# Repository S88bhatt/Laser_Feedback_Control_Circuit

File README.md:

# Laser Feedback Control Circuit
Contains all files in separate folders for the laser feedback control circuit.

## KiCAD
KiCAD Files that are up to date with the most recent and correct version of the circuit, including the PCB layout, schematic, and libraries for footprints and schematic components.

## Gimp
GIMP files which are used for laser cutting the box plating, allowing for a cleaner finish on the final product.

## FreeCAD
FreeCAD files are currently used to cut the box plating into the correct shape.

## Images
Images that show what the physical board looks like once complete.

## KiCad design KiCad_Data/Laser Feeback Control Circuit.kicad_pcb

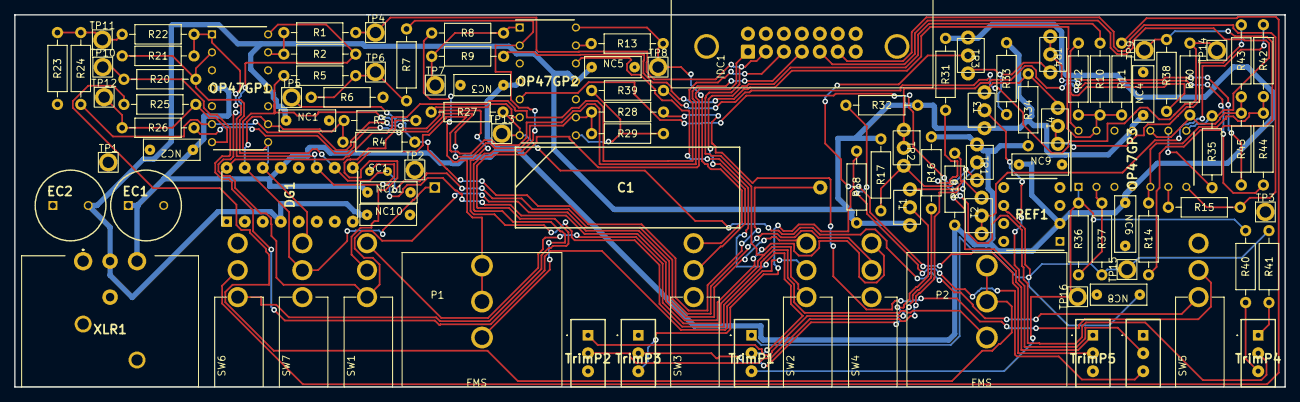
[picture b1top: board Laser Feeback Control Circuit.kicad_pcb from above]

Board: 2 copper layers, 179.6 x 52.6 mm, 105 parts (1 on the bottom side), 65 nets.

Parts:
C1: 1uF; Polypropylene Capacitor
DG1: P/N: ADG201AKNZ; ADG201AKNZ
EC1, EC2: 1000uF; ELECTROLYTIC CAPACITOR - EEU-EB1C102
IDC1: Male 14 Position IDC Connector, Digikey P/N: 609-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; Male IDC Connector
NC1, NC2, NC3, NC4, NC5, NC6, NC8, NC9, NC10, NC11: 0.1uF; CAPACITOR - 399-4209-ND
OP47GP1, OP47GP2, OP47GP3: OP470GPZ
P1, P2: 50k; Potentiometer
R1, R2, R3, R4, R8, R9, R10, R11, R12, R14, R17, R19, R20, R21, R26, R28, R29, R33, R34, R36, R37: 10k; R_Axial_DIN0207_L6.3mm_D2.5mm_P10.16mm_Horizontal
R5, R22, R38, R39, R42, R43, R44, R45: 0k; R_Axial_DIN0207_L6.3mm_D2.5mm_P10.16mm_Horizontal
R6, R23: Open; R_Axial_DIN0207_L6.3mm_D2.5mm_P10.16mm_Horizontal
R7, R13, R15, R24, R25, R27, R35: 1k; R_Axial_DIN0207_L6.3mm_D2.5mm_P10.16mm_Horizontal
R16, R18: 5k; R_Axial_DIN0207_L6.3mm_D2.5mm_P10.16mm_Horizontal
R30, R31, R32, R40, R41: 20k; R_Axial_DIN0207_L6.3mm_D2.5mm_P10.16mm_Horizontal
REF1: REF02 P/N: REF02CPZ; REF02CPZ
SC1: 1nF; Small Capacitor
SW1, SW2, SW3, SW4, SW5, SW6, SW7: SPDT Switch, P/N: 7101SD9AV2BE; AV2_Switch
T1, T2, T3, T4: Transistor P/N: 2N3906; Both_Transisitor
TP1, TP2, TP3, TP4, TP5, TP6, TP7, TP8, TP9, TP10, TP11, TP12, TP13, TP14, TP15, TP16: TestPoint
TR1, TR2, TR3, TR4: Transistor P/N: 2N3904; Both_Transisitor
TrimP1: 20k; 3296X1104LF -TrimPot
TrimP2, TrimP3, TrimP4: 10k; 3296X1104LF -TrimPot
TrimP5, TrimP6: 5k; 3296X1104LF -TrimPot
XLR1: XLR P/N: NC3MBH; NC3MBH_XLR

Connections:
+5V: NC8.1 (2), R37.1, R41.2, REF1.6 (VOUT), TP15.1, TrimP1.1
+15V: DG1.13 (V+), EC1.1, NC2.1 (2), NC3.1 (2), NC6.1 (2), NC9.1 (2), NC11.1 (2), OP47GP1.4 (+V), OP47GP2.4 (+V), OP47GP3.4 (+V), R16.1, R19.1, R31.1, R34.1, REF1.2 (VIN), TR1.1 (C), TR3.1 (C), XLR1.2 (+15V)
-5V: OP47GP3.1, R36.2, R40.1, TP16.1, TrimP1.3
-15V: DG1.4 (V-), EC2.2, NC1.1 (2), NC4.1 (2), NC5.1 (2), NC10.1 (2), OP47GP1.11 (V-), OP47GP2.11 (V-), OP47GP3.11 (V-), R17.1, R18.2, R32.2, R33.1, T1.1 (C), T3.1 (C), XLR1.3 (-15V)
GND: DG1.5 (GND), EC1.2, EC2.1, IDC1.7 (C), IDC1.8 (G), IDC1.9 (G), IDC1.10 (G), IDC1.11 (G), IDC1.12 (G), IDC1.13 (G), IDC1.14 (G), NC1.2 (1), NC2.2 (1), NC3.2 (1), NC4.2 (1), NC5.2 (1), NC6.2 (1), NC8.2 (1), NC9.2 (1), NC10.2 (1), NC11.2 (1), OP47GP1.3 (+), OP47GP1.5 (+), OP47GP1.10 (+), OP47GP1.12 (+), OP47GP2.3 (+), OP47GP2.10 (+), OP47GP3.3 (+), OP47GP3.12 (+), R6.1, R23.2, REF1.4 (GND), SW3.1 (A), SW5.3 (C), SW6.3 (C), TP1.1, TP2.1, TP3.1, TrimP2.3, TrimP3.1, TrimP5.3, TrimP6.1, XLR1.1 (GNDC), XLR1.G1
unnamed: C1.1, DG1.15 (D2), OP47GP1.9 (-), R3.2, R4.1, SW7.2 (B)
unnamed: DG1.16 (IN2), IDC1.3 (C)
unnamed: C1.2, DG1.14 (S2), OP47GP1.8, R4.2, R5.1, SW7.3 (C)
unnamed: DG1.10 (D3), OP47GP1.2 (-), R20.2, R21.1, SC1.1, SW4.2 (B)
unnamed: DG1.9 (IN3), IDC1.4 (C)
unnamed: DG1.11 (S3), OP47GP1.1, R21.2, R22.1, SC1.2, SW4.3 (C)
unnamed: IDC1.5 (C), OP47GP3.8, R35.2
unnamed: IDC1.6 (C), OP47GP3.7, R15.2
unnamed: OP47GP1.7, R25.2, R26.1, TP12.1
unnamed: OP47GP1.6 (-), P2.1, R24.2
unnamed: OP47GP1.13 (-), R1.2, R2.1
unnamed: OP47GP2.1, R8.2, R9.1, TP7.1
unnamed: OP47GP2.8, R29.2, R39.1
unnamed: OP47GP2.2 (-), P1.1, R7.2
unnamed: OP47GP2.5 (+), TrimP4.2
unnamed: OP47GP2.6 (-), R27.1
unnamed: OP47GP2.9 (-), R26.2, R28.1, R29.1
unnamed: OP47GP2.12 (+), TrimP1.2
unnamed: OP47GP2.13 (-), R13.1
unnamed: OP47GP3.14, R12.2, R38.1
unnamed: OP47GP3.2 (-), R36.1, R37.2
unnamed: OP47GP3.5 (+), R14.2, R42.2, R44.2
unnamed: OP47GP3.6 (-), R15.1
unnamed: OP47GP3.10 (+), R30.2, R43.2, R45.2
unnamed: OP47GP3.9 (-), R35.1
unnamed: OP47GP3.13 (-), R9.2, R10.1, R11.2, R12.1
unnamed: P1.2, P1.3, R8.1
unnamed: P2.2, P2.3, R25.1
unnamed: R5.2, R6.2, R7.1, TP6.1
unnamed: R14.1, R38.2, TP9.1
unnamed: R16.2, TrimP2.1
unnamed: R18.1, TrimP3.3
unnamed: R22.2, R23.1, R24.1, TP11.1
unnamed: R30.1, R39.2, TP14.1
unnamed: R31.2, TrimP5.1
unnamed: R32.1, TrimP6.3
unnamed: R40.2, TrimP4.3
unnamed: R41.1, TrimP4.1
unnamed: OP47GP1.14, R2.2, SW1.1 (A), SW2.3 (C)
unnamed: R3.1, SW1.2 (B), TP5.1
unnamed: IDC1.2 (C), R1.1, SW1.3 (C), SW2.1 (A), TP4.1
unnamed: R20.1, SW2.2 (B), TP10.1
unnamed: R10.2, SW3.2 (B)
unnamed: OP47GP2.14, R13.2, SW3.3 (C), TP8.1
unnamed: OP47GP2.7, R27.2, SW5.1 (A), TP13.1
unnamed: R28.2, SW5.2 (B)
unnamed: IDC1.1 (C), SW6.1 (A)
unnamed: R11.1, SW6.2 (B)
unnamed: T1.2 (B), TrimP3.2
unnamed: R19.2, T1.3 (E), T2.3 (E)
unnamed: R42.1, T2.1 (C), T2.2 (B)
unnamed: T3.2 (B), TrimP6.2
unnamed: R34.2, T3.3 (E), T4.3 (E)
unnamed: R43.1, T4.1 (C), T4.2 (B)
unnamed: TR1.2 (B), TrimP2.2
unnamed: R17.2, TR1.3 (E), TR2.3 (E)
unnamed: R44.1, TR2.1 (C), TR2.2 (B)
unnamed: TR3.2 (B), TrimP5.2
unnamed: R33.2, TR3.3 (E), TR4.3 (E)
unnamed: R45.1, TR4.1 (C), TR4.2 (B)

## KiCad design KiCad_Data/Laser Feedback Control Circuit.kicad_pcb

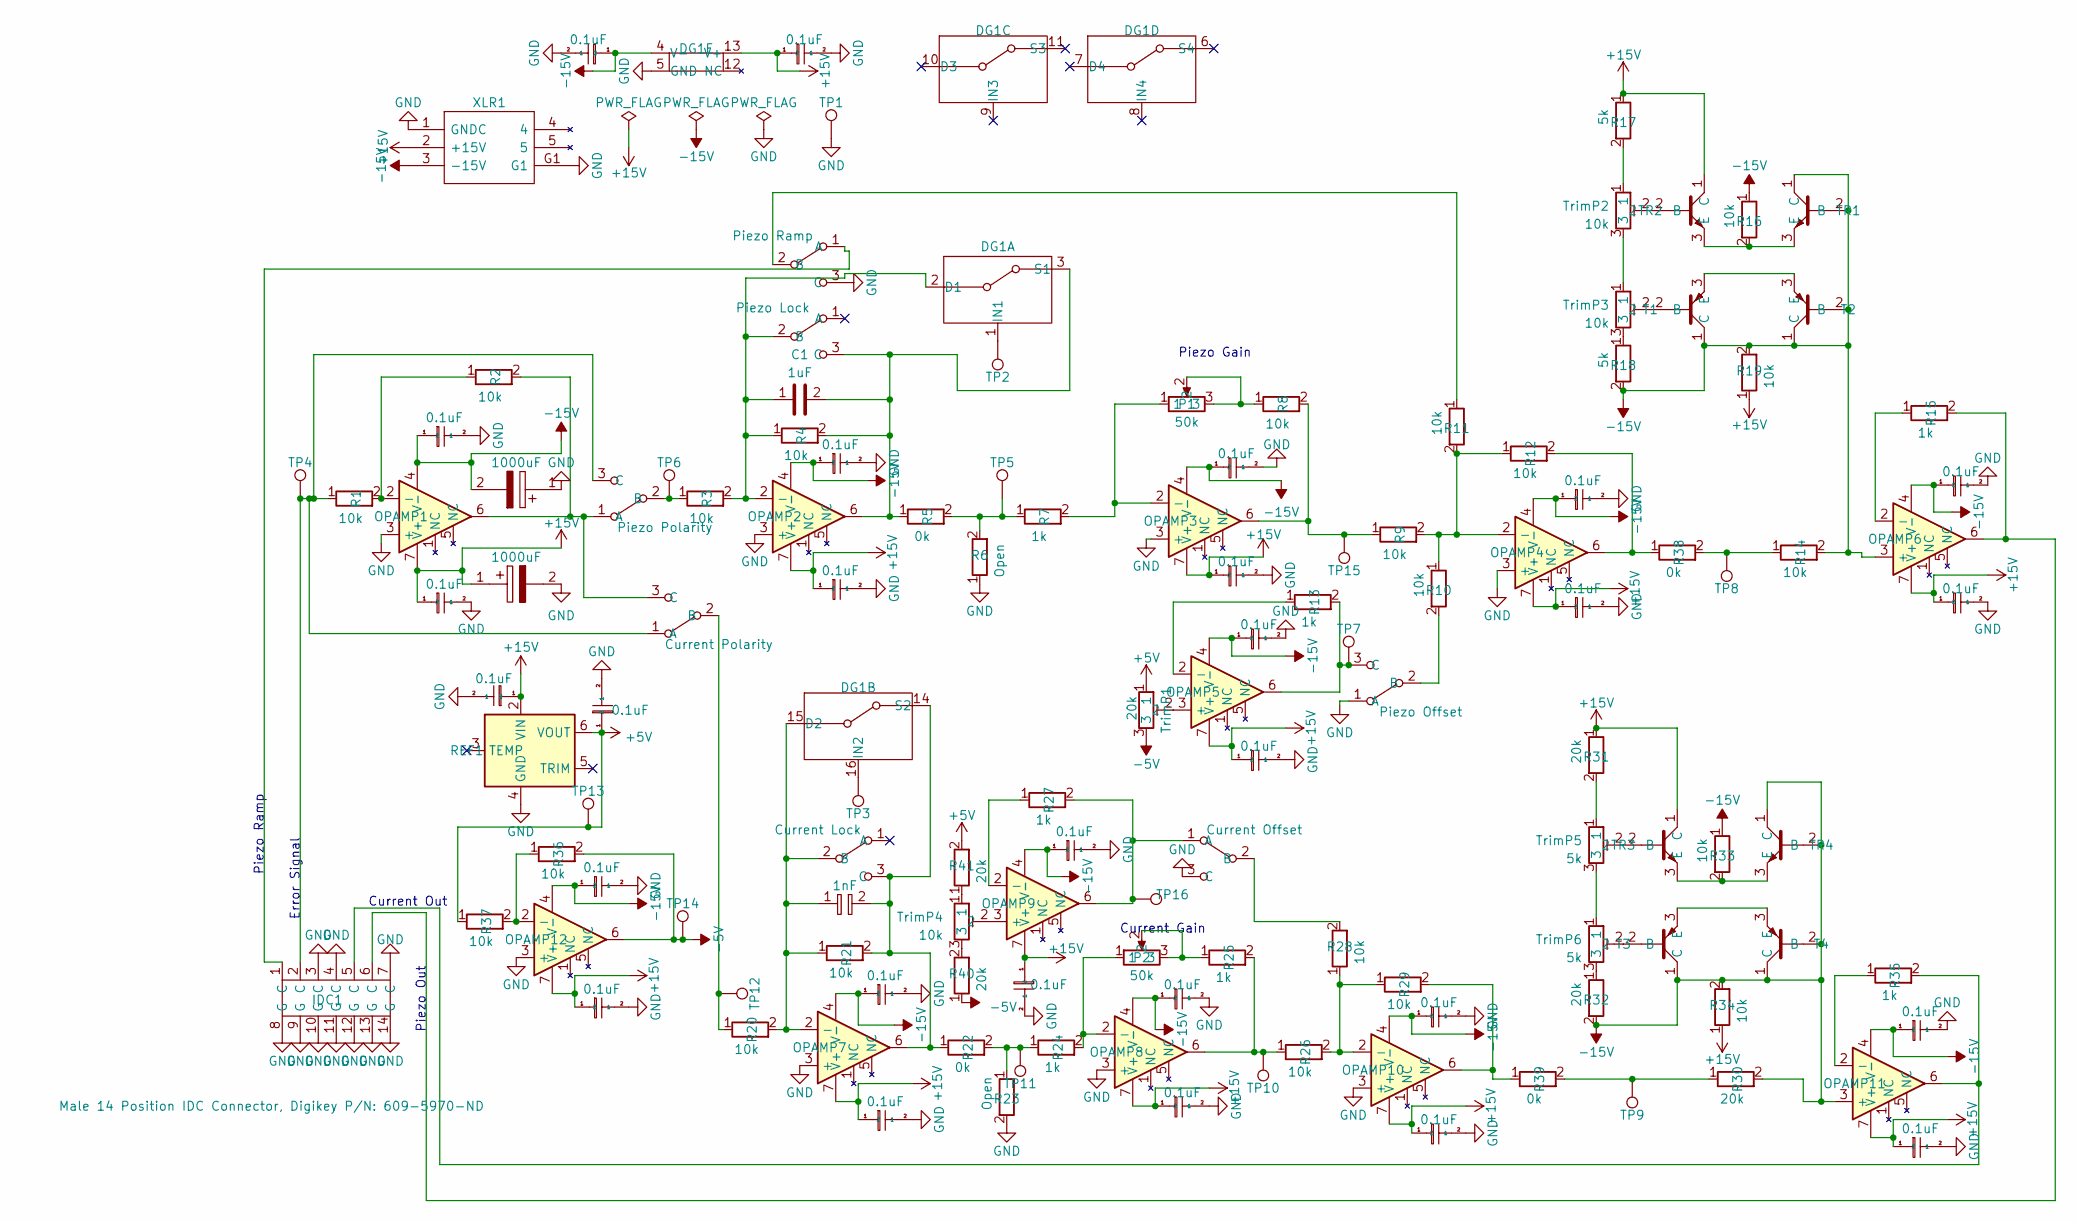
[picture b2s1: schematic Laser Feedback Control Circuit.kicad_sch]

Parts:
C1: 1uF; Polypropylene Capacitor
DG1: P/N: ADG201AKNZ; ADG201AKNZ; Mouser Part Number 781-DG201HSDY-T1-E3
EC1, EC2: 1000uF; ELECTROLYTIC CAPACITOR - EEU-EB1C102
IDC1: Male 14 Position IDC Connector, Digikey P/N: 609-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; Male IDC Connector
NC1, NC2, NC3, NC4, NC5, NC6, NC7, NC8, NC9, NC10, NC11, NC12, NC13, NC14, NC15, NC16, NC17, NC18, NC19, NC20, NC21, NC22, NC23, NC24, NC25, NC26, NC27, NC28: 0.1uF; CAPACITOR - 399-4209-ND
OPAMP1, OPAMP2, OPAMP3, OPAMP4, OPAMP5, OPAMP6, OPAMP7, OPAMP8, OPAMP9, OPAMP10, OPAMP11, OPAMP12: P/N: OPA27GP; OPA27GP_Operational_Amplifier
P1, P2: 50k; Potentiometer
R1, R2, R3, R4, R8, R9, R10, R11, R12, R14, R16, R19, R20, R21, R26, R28, R29, R33, R34, R36, R37: 10k; R_Axial_DIN0207_L6.3mm_D2.5mm_P10.16mm_Horizontal
R5, R22, R38, R39: 0k; R_Axial_DIN0207_L6.3mm_D2.5mm_P10.16mm_Horizontal
R6, R23: Open; R_Axial_DIN0207_L6.3mm_D2.5mm_P10.16mm_Horizontal
R7, R13, R15, R24, R25, R27, R35: 1k; R_Axial_DIN0207_L6.3mm_D2.5mm_P10.16mm_Horizontal
R17, R18: 5k; R_Axial_DIN0207_L6.3mm_D2.5mm_P10.16mm_Horizontal
R30, R31, R32, R40, R41: 20k; R_Axial_DIN0207_L6.3mm_D2.5mm_P10.16mm_Horizontal
REF1: REF02 P/N: REF02CPZ; REF02CPZ
SC1: 1nF; Small Capacitor
SW1, SW2, SW3, SW4, SW5, SW6, SW7: SPDT Switch, P/N: 7101SD9AV2BE; AV2_Switch
T1, T2, T3, T4: Transistor P/N: 2N3906; Both_Transisitor
TP1, TP2, TP3, TP4, TP5, TP6, TP7, TP8, TP9, TP10, TP11, TP12, TP13, TP14, TP15, TP16: TestPoint
TR1, TR2, TR3, TR4: Transistor P/N: 2N3904; Both_Transisitor
TrimP1: 20k; 3296X1104LF -TrimPot
TrimP2, TrimP3, TrimP4: 10k; 3296X1104LF -TrimPot
TrimP5, TrimP6: 5k; 3296X1104LF -TrimPot
XLR1: XLR P/N: NC3MBH; NC3MBH

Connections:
+5V: NC27.1 (2), R37.1, R41.2, REF1.6 (VOUT), TP13.1, TrimP1.1
+15V: DG1.13 (V+), EC1.1, NC2.1 (2), NC4.1 (2), NC6.1 (2), NC8.1 (2), NC10.1 (2), NC12.1 (2), NC14.1 (2), NC16.1 (2), NC18.1 (2), NC20.1 (2), NC22.1 (2), NC24.1 (2), NC26.1 (2), NC28.1 (2), OPAMP1.7 (V+), OPAMP2.7 (V+), OPAMP3.7 (V+), OPAMP4.7 (V+), OPAMP5.7 (V+), OPAMP6.7 (V+), OPAMP7.7 (V+), OPAMP8.7 (V+), OPAMP9.7 (V+), OPAMP10.7 (V+), OPAMP11.7 (V+), OPAMP12.7 (V+), R17.1, R19.1, R31.1, R34.1, REF1.2 (VIN), TR2.1 (C), TR3.1 (C), XLR1.2 (+15V)
-5V: OPAMP12.6, R36.2, R40.1, TP14.1, TrimP1.3
-15V: DG1.4 (V-), EC2.2, NC1.1 (2), NC3.1 (2), NC5.1 (2), NC7.1 (2), NC9.1 (2), NC11.1 (2), NC13.1 (2), NC15.1 (2), NC17.1 (2), NC19.1 (2), NC21.1 (2), NC23.1 (2), NC25.1 (2), OPAMP1.4 (V-), OPAMP2.4 (V-), OPAMP3.4 (V-), OPAMP4.4 (V-), OPAMP5.4 (V-), OPAMP6.3 (+), OPAMP6.4 (V-), OPAMP7.4 (V-), OPAMP8.4 (V-), OPAMP9.4 (V-), OPAMP10.4 (V-), OPAMP11.3 (+), OPAMP11.4 (V-), OPAMP12.4 (V-), R14.2, R16.1, R18.2, R19.2, R30.2, R32.2, R33.1, R34.2, T1.1 (C), T2.1 (C), T2.2 (B), T3.1 (C), T4.1 (C), T4.2 (B), TR1.1 (C), TR1.2 (B), TR4.1 (C), TR4.2 (B), XLR1.3 (-15V)
GND: DG1.5 (GND), EC1.2, EC2.1, IDC1.3 (C), IDC1.4 (C), IDC1.7 (C), IDC1.8 (G), IDC1.9 (G), IDC1.10 (G), IDC1.11 (G), IDC1.12 (G), IDC1.13 (G), IDC1.14 (G), NC1.2 (1), NC2.2 (1), NC3.2 (1), NC4.2 (1), NC5.2 (1), NC6.2 (1), NC7.2 (1), NC8.2 (1), NC9.2 (1), NC10.2 (1), NC11.2 (1), NC12.2 (1), NC13.2 (1), NC14.2 (1), NC15.2 (1), NC16.2 (1), NC17.2 (1), NC18.2 (1), NC19.2 (1), NC20.2 (1), NC21.2 (1), NC22.2 (1), NC23.2 (1), NC24.2 (1), NC25.2 (1), NC26.2 (1), NC27.2 (1), NC28.2 (1), OPAMP1.3 (+), OPAMP2.3 (+), OPAMP3.3 (+), OPAMP4.3 (+), OPAMP7.3 (+), OPAMP8.3 (+), OPAMP10.3 (+), OPAMP12.3 (+), R6.1, R23.2, REF1.4 (GND), SW3.1 (A), SW5.3 (C), SW6.3 (C), TP1.1, XLR1.1 (GNDC), XLR1.G1
unnamed: C1.1, DG1.2 (D1), OPAMP2.2 (-), R3.2, R4.1, SW7.2 (B)
unnamed: DG1.1 (IN1), TP2.1
unnamed: C1.2, DG1.3 (S1), OPAMP2.6, R4.2, R5.1, SW7.3 (C)
unnamed: DG1.15 (D2), OPAMP7.2 (-), R20.2, R21.1, SC1.1, SW4.2 (B)
unnamed: DG1.16 (IN2), TP3.1
unnamed: DG1.14 (S2), OPAMP7.6, R21.2, R22.1, SC1.2, SW4.3 (C)
unnamed: IDC1.5 (C), OPAMP11.6, R35.2
unnamed: IDC1.6 (C), OPAMP6.6, R15.2
unnamed: OPAMP1.2 (-), R1.2, R2.1
unnamed: OPAMP3.2 (-), P1.1, R7.2
unnamed: OPAMP3.6, R8.2, R9.1, TP15.1
unnamed: OPAMP4.2 (-), R9.2, R10.1, R11.2, R12.1
unnamed: OPAMP4.6, R12.2, R38.1
unnamed: OPAMP5.3 (+), TrimP1.2
unnamed: OPAMP5.2 (-), R13.1
unnamed: OPAMP6.2 (-), R15.1
unnamed: OPAMP8.2 (-), P2.1, R24.2
unnamed: OPAMP8.6, R25.2, R26.1, TP10.1
unnamed: OPAMP9.3 (+), TrimP4.2
unnamed: OPAMP9.2 (-), R27.1
unnamed: OPAMP10.2 (-), R26.2, R28.1, R29.1
unnamed: OPAMP10.6, R29.2, R39.1
unnamed: OPAMP11.2 (-), R35.1
unnamed: OPAMP12.2 (-), R36.1, R37.2
unnamed: P1.2, P1.3, R8.1
unnamed: P2.2, P2.3, R25.1
unnamed: R5.2, R6.2, R7.1, TP5.1
unnamed: R14.1, R38.2, TP8.1
unnamed: R17.2, TrimP2.1
unnamed: R18.1, TrimP3.3
unnamed: R22.2, R23.1, R24.1, TP11.1
unnamed: R30.1, R39.2, TP9.1
unnamed: R31.2, TrimP5.1
unnamed: R32.1, TrimP6.3
unnamed: R40.2, TrimP4.3
unnamed: R41.1, TrimP4.1
unnamed: OPAMP1.6, R2.2, SW1.1 (A), SW2.3 (C)
unnamed: R3.1, SW1.2 (B), TP6.1
unnamed: IDC1.2 (C), R1.1, SW1.3 (C), SW2.1 (A), TP4.1
unnamed: R20.1, SW2.2 (B), TP12.1
unnamed: R10.2, SW3.2 (B)
unnamed: OPAMP5.6, R13.2, SW3.3 (C), TP7.1
unnamed: OPAMP9.6, R27.2, SW5.1 (A), TP16.1
unnamed: R28.2, SW5.2 (B)
unnamed: IDC1.1 (C), SW6.1 (A)
unnamed: R11.1, SW6.2 (B)
unnamed: T1.2 (B), TrimP3.2
unnamed: T1.3 (E), T2.3 (E)
unnamed: T3.2 (B), TrimP6.2
unnamed: T3.3 (E), T4.3 (E)
unnamed: R16.2, TR1.3 (E), TR2.3 (E)
unnamed: TR2.2 (B), TrimP2.2
unnamed: TR3.2 (B), TrimP5.2
unnamed: R33.2, TR3.3 (E), TR4.3 (E)
unnamed: TrimP2.3, TrimP3.1
unnamed: TrimP5.3, TrimP6.1

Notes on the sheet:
Current Gain
Error Signal
Piezo Gain
Current Out
Piezo Out
Piezo Ramp

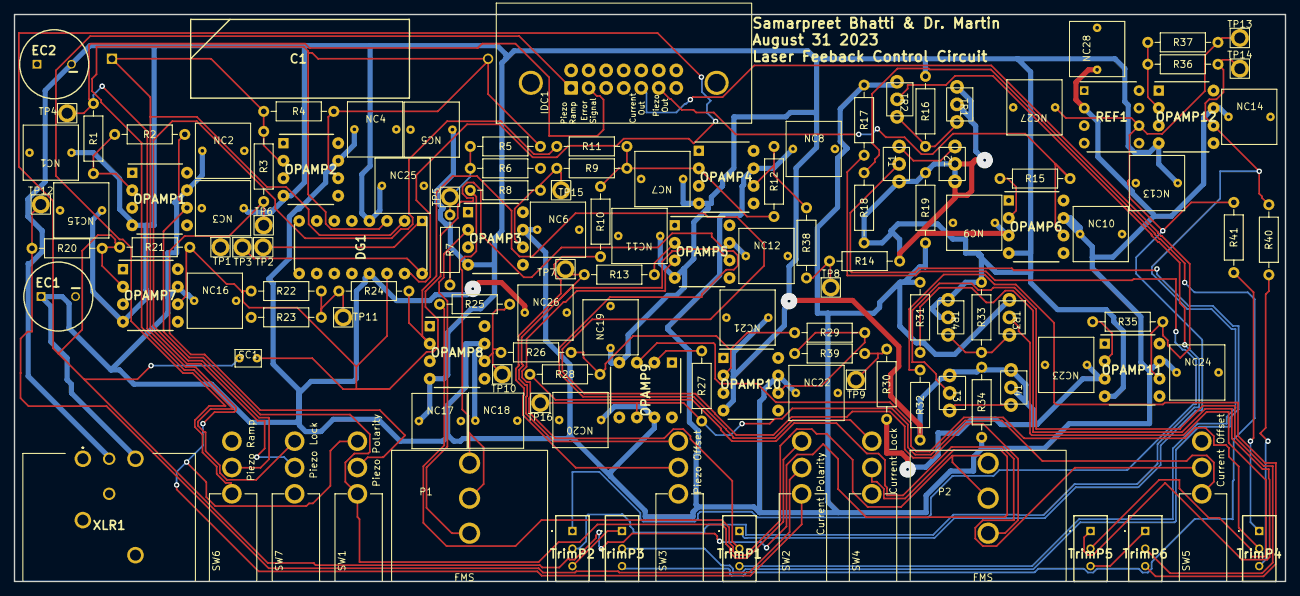
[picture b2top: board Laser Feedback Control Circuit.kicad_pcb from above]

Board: 2 copper layers, 184.2 x 82.1 mm, 128 parts (0 on the bottom side), 61 nets.

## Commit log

2023-08-06 Create Readme-kicad
2023-08-06 Added KiCad Files
2023-08-07 Made small corrections regarding ground fill
2023-08-14 Updated files
    Contain Kicad files which include the required capacitors on each op-amp, and additionally electrolytic capacitors were added
2023-08-14 Not required
    Autosave of the current PCB layout kicad makes these occasionally to constantly save progress
2023-08-16 Updated PCB and Schematic
    The PCB has the same changes as the schematic, the schematic had the DPDT switch made into 2 separate switches and capacitors were added onto the DG201 switch's
2023-08-16 Fixed minor DRC issue with clearance
2023-08-16 Fixed minor ground fill issue
    Not a critical issue for review, just wires were adjusted so ground fill is fixed
2023-08-16 Changed Names
    Naming was updated for the symbols to make more sense (adding values for resistance, what each switch does, etc)
2023-08-16 better name
2023-08-17 Fixed Wiring that was close to edge
    This version is our first ordered version
2023-08-17 Changed names
2023-08-17 Added footprints separately
2023-08-17 Delete ReadMe
    Only made to create the folder
2023-08-17 Added Cutout
    This cutout uses this box 1455U1601 currently. It is not complete since the trim pots need to be measured before I can adjust the height of them
2023-08-23 Updated Version
2023-08-24 Added Gimp file
2023-09-06 Corrected measurements, and added gcode + .stl file
2023-09-07 Updated measurements
2023-09-14 Updated dimensions
2023-09-15 Finding error
    Increased dimensions of all circles at top by 1mm for diameter to find which is causing a problem, the only exception is the XLR which is what every other position is relative to
2023-09-21 Updated measurements
    Adjusted measurements for each individual piece, added a bar in the middle to stop bending
2023-09-25 Updated IDC connections
2023-09-29 Updated files
2023-09-29 Delete FreeCad_Data/Laser_Feedback_Control_Cirucuit_Cut-Extrude_3DPrint.gcode
    Bad Gcode used, ABS was used instead of PLA when slicing
2023-10-20 Create Read
2023-10-21 Update images
2023-10-21 Delete Images/images
    Just a test on IOS, but IOS is not ideal for github use
2023-10-21 Added images
2023-11-06 Update README.md
    Better description
2023-11-12 .\Laser Feedback Control Circuit Footprints.pretty"
2023-11-12 Most Up To Date Version
2024-02-07 Circuit after correction
    Corrections made included:
    - Using quad op-amps which reduced the space needed for the board, however, this made running traces more complicated.
    - There was an error with how the IDC connector was set up in this, and all the pins had to be adjusted.
    - The circuit that limited the maximum and minimum voltages at the end had a correction added where the previous version had a misconnected trace which caused the whole circuit not to function proper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
